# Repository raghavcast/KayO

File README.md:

# KayO
Head to releases and download the newest version.

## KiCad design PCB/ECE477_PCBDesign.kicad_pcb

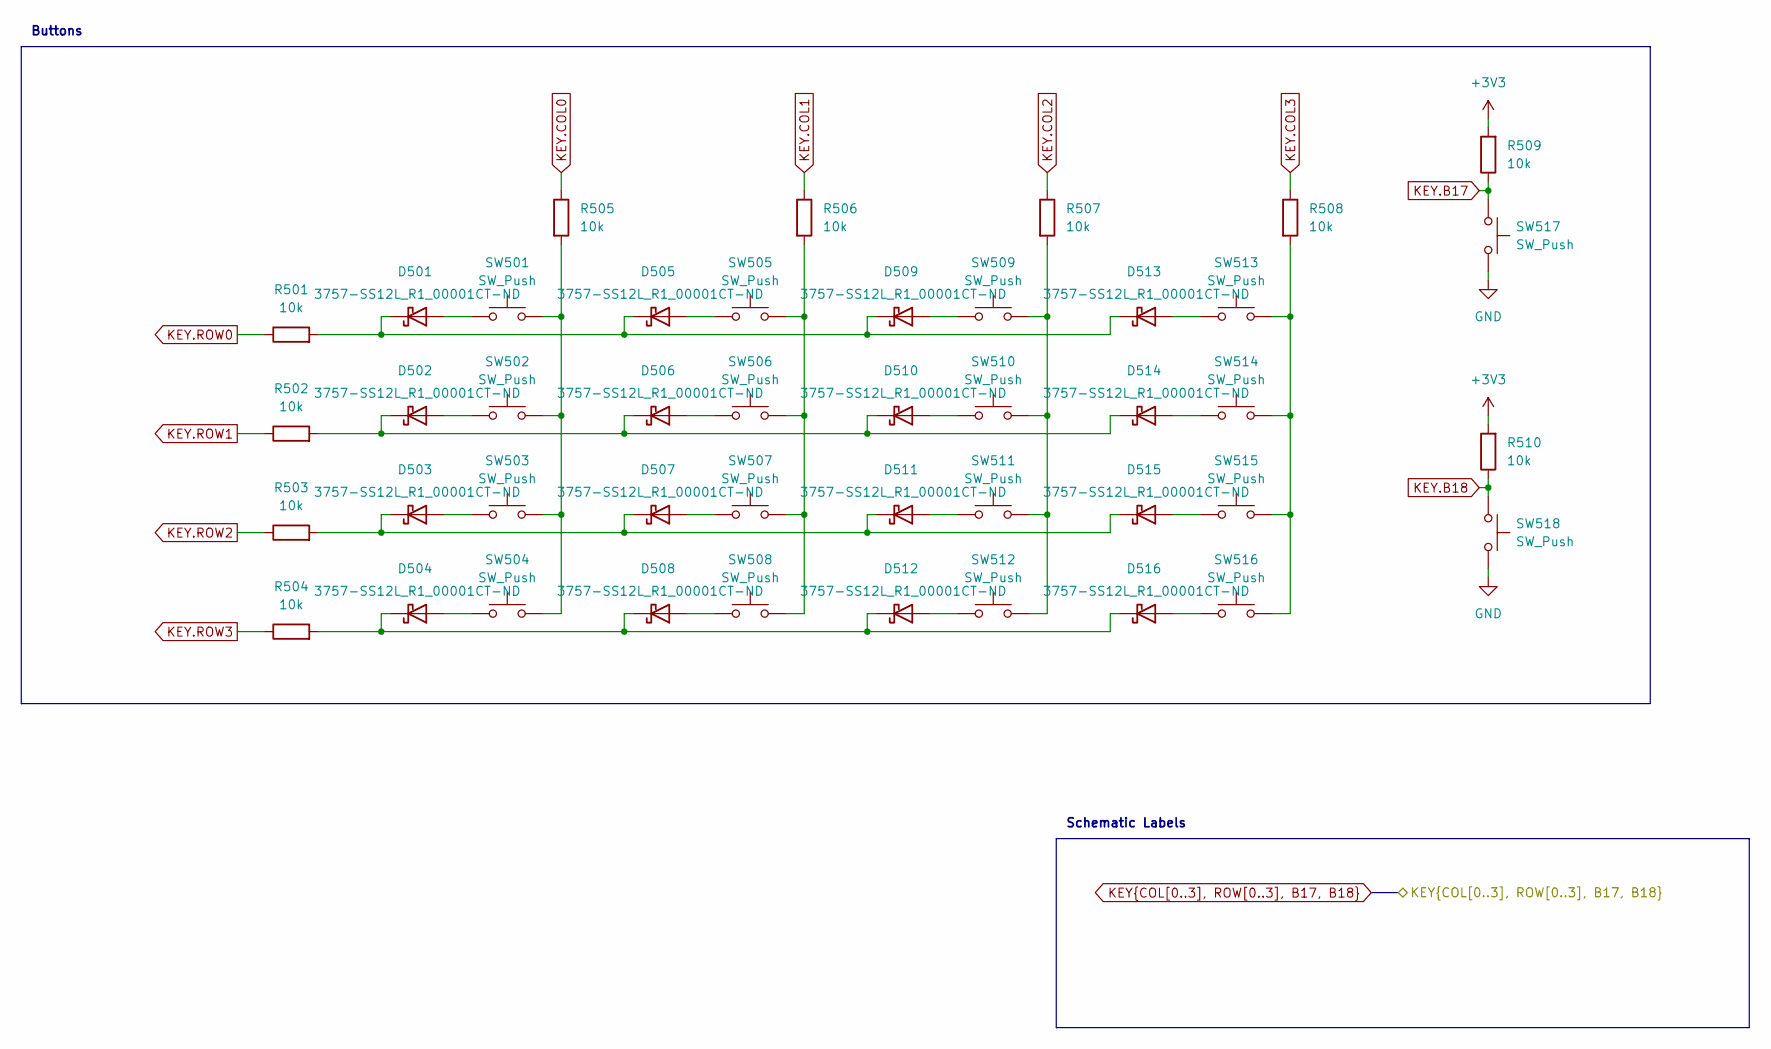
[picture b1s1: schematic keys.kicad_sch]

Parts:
D501, D502, D503, D504, D505, D506, D507, D508, D509, D510, D511, D512, D513, D514, D515, D516: 3757-SS12L_R1_00001CT-ND; D_SMA; Mfg. Part # SS12L_R1_00001; LCSC C36975
R501, R502, R503, R504, R505, R506, R507, R508, R509, R510: 10k; R_0603_1608Metric_Pad0.98x0.95mm_HandSolder; Mfg. Part # RC0603JR-0710KL; DigiKey Part 311-10KGRCT-ND
SW501, SW502, SW503, SW504, SW505, SW506, SW507, SW508, SW509, SW510, SW511, SW512, SW513, SW514, SW515, SW516, SW517, SW518: SW_Push; JST_XH_B2B-XH-A_1x02_P2.50mm_Vertical; Mfg. Part # B2B-XH-A; DigiKey Part 455-B2B-XH-A-ND

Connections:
+3V3: R509.2, R510.2; also elsewhere on the board
GND: SW517.2, SW518.2; also elsewhere on the board
KEY.B17: R509.1, SW517.1; also elsewhere on the board
KEY.B18: R510.1, SW518.1; also elsewhere on the board
KEY.COL0: R505.1; also elsewhere on the board
KEY.COL1: R506.1; also elsewhere on the board
KEY.COL2: R507.1; also elsewhere on the board
KEY.COL3: R508.1; also elsewhere on the board
KEY.ROW0: R501.1; also elsewhere on the board
KEY.ROW1: R502.1; also elsewhere on the board
KEY.ROW2: R503.1; also elsewhere on the board
KEY.ROW3: R504.1; also elsewhere on the board
unnamed: D501.2 (A), SW501.1
unnamed: D501.1 (K), D505.1 (K), D509.1 (K), D513.1 (K), R501.2
unnamed: D502.2 (A), SW502.1
unnamed: D502.1 (K), D506.1 (K), D510.1 (K), D514.1 (K), R502.2
unnamed: D503.2 (A), SW503.1
unnamed: D503.1 (K), D507.1 (K), D511.1 (K), D515.1 (K), R503.2
unnamed: D504.2 (A), SW504.1
unnamed: D504.1 (K), D508.1 (K), D512.1 (K), D516.1 (K), R504.2
unnamed: D505.2 (A), SW505.1
unnamed: D506.2 (A), SW506.1
unnamed: D507.2 (A), SW507.1
unnamed: D508.2 (A), SW508.1
unnamed: D509.2 (A), SW509.1
unnamed: D510.2 (A), SW510.1
unnamed: D511.2 (A), SW511.1
unnamed: D512.2 (A), SW512.1
unnamed: D513.2 (A), SW513.1
unnamed: D514.2 (A), SW514.1
unnamed: D515.2 (A), SW515.1
unnamed: D516.2 (A), SW516.1
unnamed: R505.2, SW501.2, SW502.2, SW503.2, SW504.2
unnamed: R506.2, SW505.2, SW506.2, SW507.2, SW508.2
unnamed: R507.2, SW509.2, SW510.2, SW511.2, SW512.2
unnamed: R508.2, SW513.2, SW514.2, SW515.2, SW516.2

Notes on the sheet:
Buttons
Schematic Labels

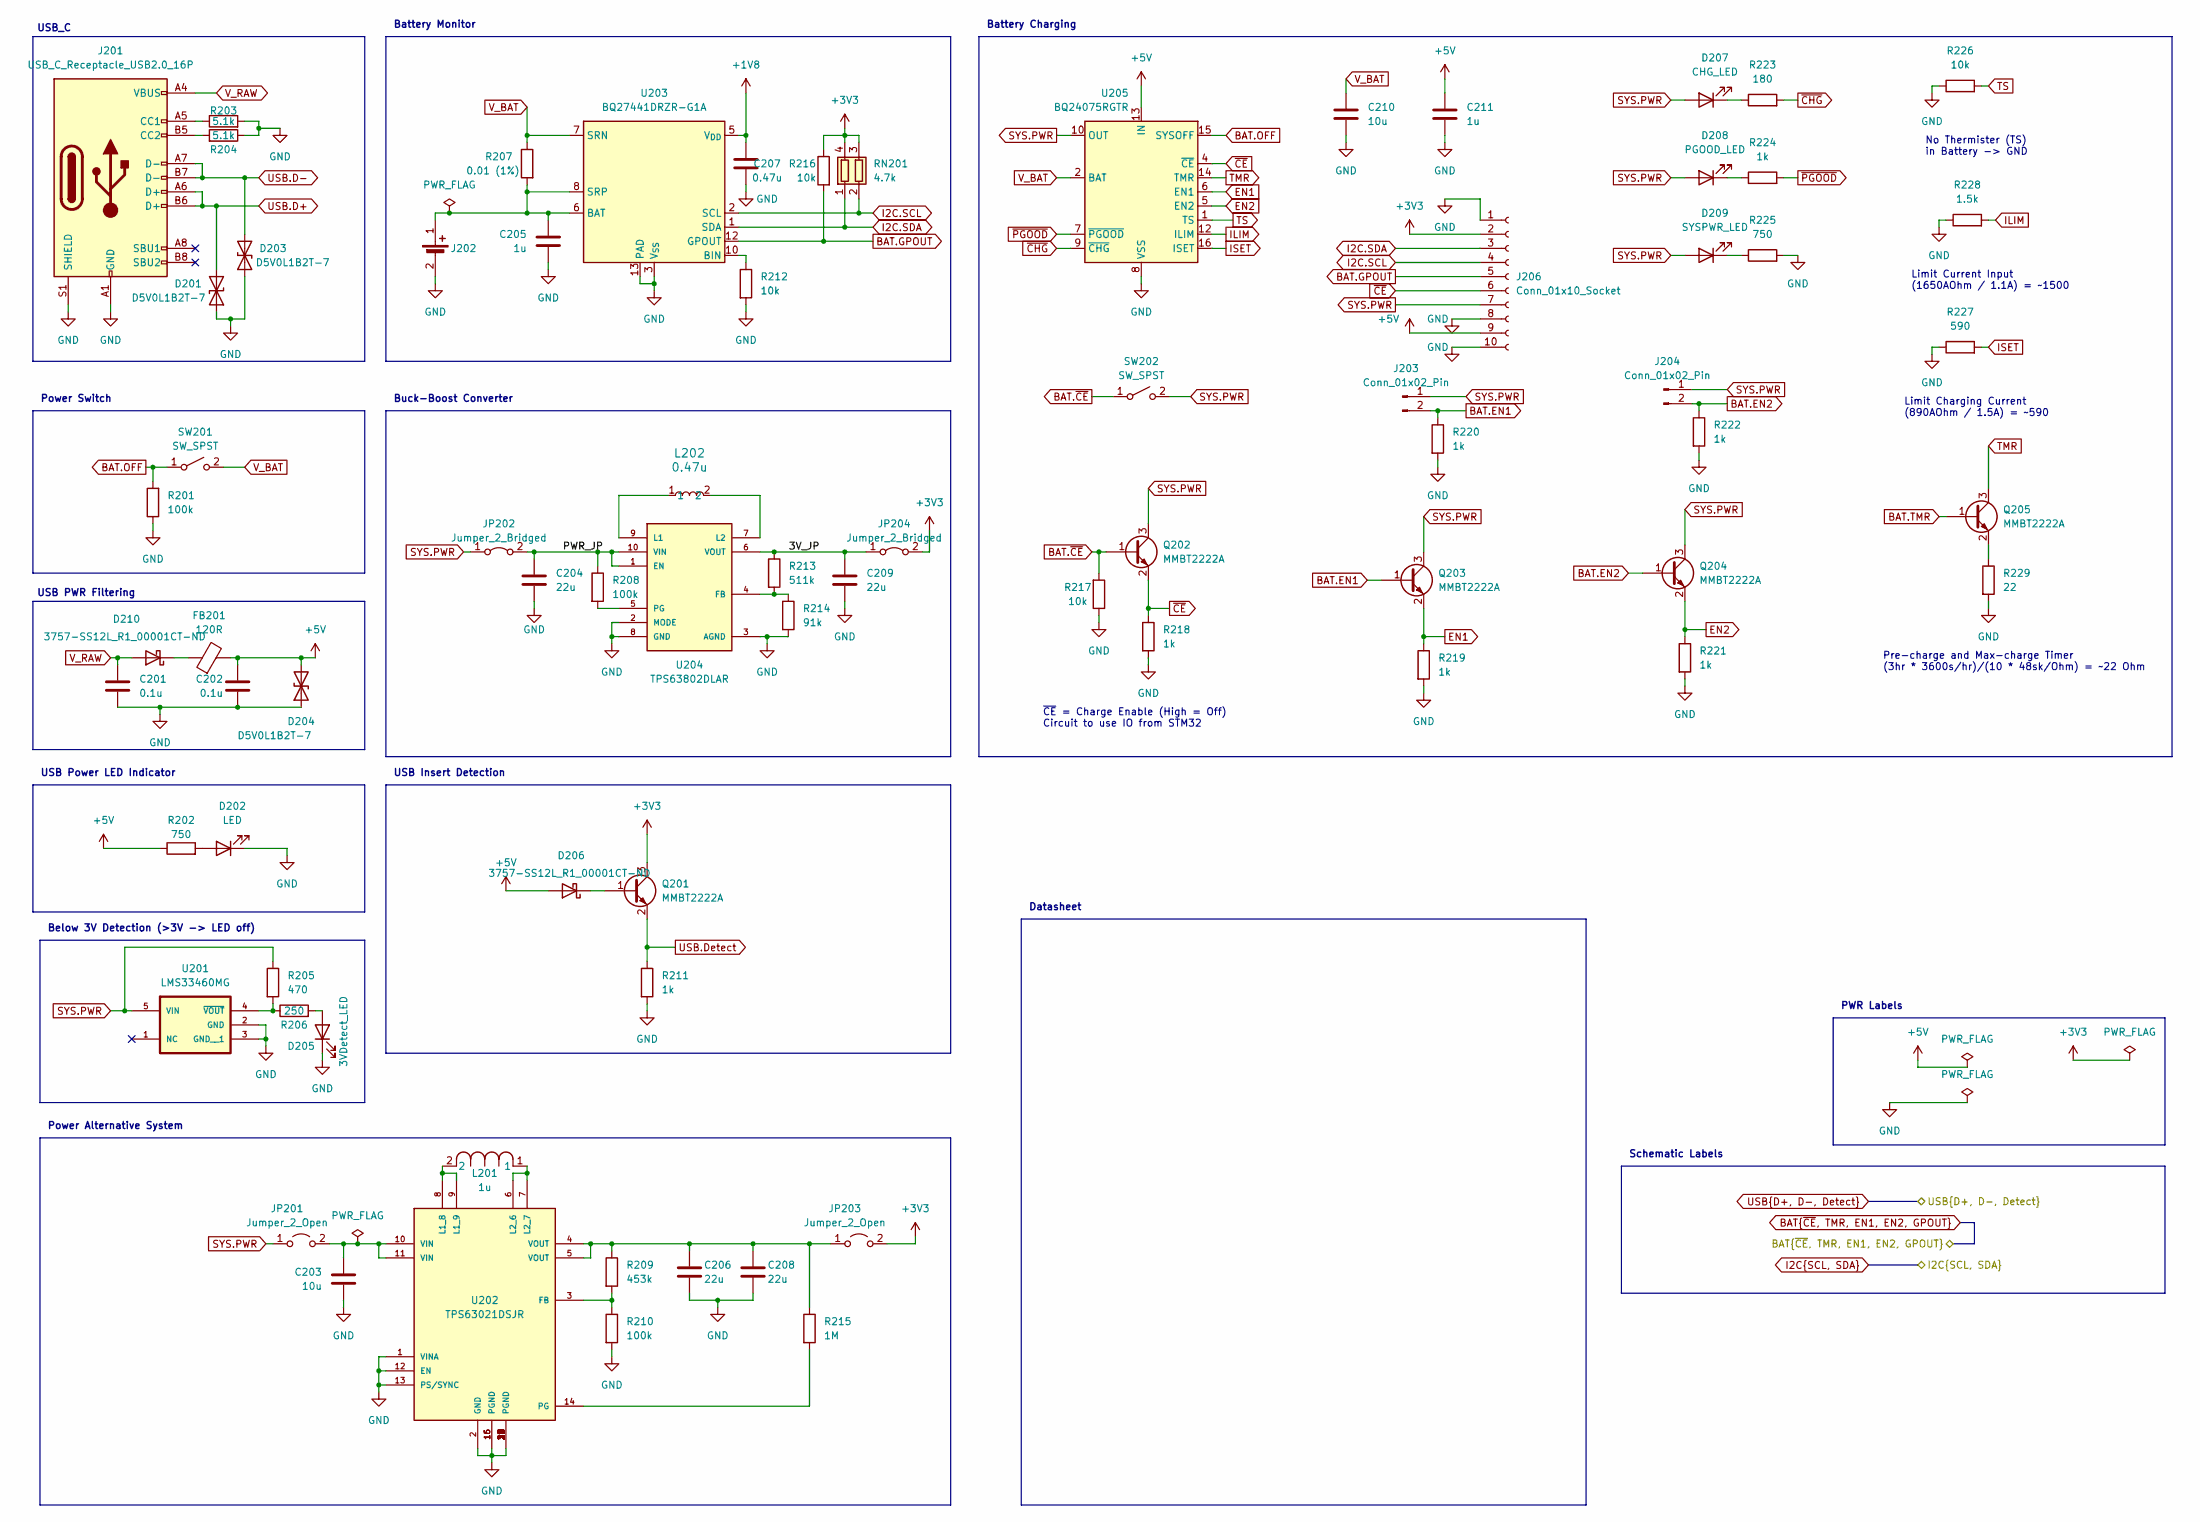
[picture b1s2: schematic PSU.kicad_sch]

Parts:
C201, C202: 0.1u; C_0603_1608Metric_Pad1.08x0.95mm_HandSolder; Mfg. Part # GRM033R61A104ME15D; LCSC C1525
C203: 10u; C_0603_1608Metric_Pad1.08x0.95mm_HandSolder; Mfg. Part # C1608X5R1E106M080AC; DigiKey Part 445-9015-1-ND
C204: 22u; C_0603_1608Metric_Pad1.08x0.95mm_HandSolder; Mfg. Part # GRM188R60J226MEA0D; DigiKey Part 490-7611-1-ND
C205, C211: 1u; C_0603_1608Metric_Pad1.08x0.95mm_HandSolder; Mfg. Part # GRM033R60J105MEA2D; DigiKey Part 490-7229-1-ND
C206, C208, C209: 22u; C_0603_1608Metric_Pad1.08x0.95mm_HandSolder; Mfg. Part # C1608X5R1A226M080AC; DigiKey Part 445-9077-1-ND
C207: 0.47u; C_0603_1608Metric_Pad1.08x0.95mm_HandSolder; Mfg. Part # C1608X7R1C474K080AC; DigiKey Part 445-5192-1-ND
C210: 10u; C_0603_1608Metric_Pad1.08x0.95mm_HandSolder; Mfg. Part # GRM188R60J106KE47J; DigiKey Part 490-GRM188R60J106KE47JCT-ND
D201, D203, D204: D5V0L1B2T-7; D_SOD-523; Mfg. Part # D5V0L1B2T-7; LCSC C508181
D202: LED; D_0805_2012Metric_Pad1.15x1.40mm_HandSolder; Mfg. Part # LS R976-NR-1; LCSC C136765
D205: 3VDetect_LED; D_0805_2012Metric_Pad1.15x1.40mm_HandSolder; Mfg. Part # LS R976-NR-1; LCSC C136765
D206, D210: 3757-SS12L_R1_00001CT-ND; D_SMA; Mfg. Part # SS12L_R1_00001; LCSC C36975
D207: CHG_LED; LED_0805_2012Metric_Pad1.15x1.40mm_HandSolder; Mfg. Part # LS R976-NR-1; DigiKey Part 475-LSR976-NR-1CT-ND
D208: PGOOD_LED; LED_0805_2012Metric_Pad1.15x1.40mm_HandSolder; Mfg. Part # LS R976-NR-1; DigiKey Part 475-LSR976-NR-1CT-ND
D209: SYSPWR_LED; LED_0805_2012Metric_Pad1.15x1.40mm_HandSolder; Mfg. Part # LS R976-NR-1; DigiKey Part 475-LSR976-NR-1CT-ND
FB201: 120R; L_0603_1608Metric; Mfg. Part # BLM18BD121SH1D; LCSC C279682
J201: USB_C_Receptacle_USB2.0_16P; USB_C_Receptacle_HRO_TYPE-C-31-M-12; Mfg. Part # USB4105-GF-A; DigiKey Part 2073-USB4105-GF-ACT-ND
J202: Conn_01x02_Pin; CONN_S2B-PH-K-S_JST; Mfg. Part # S2B-PH-K-S; DigiKey Part 455-1719-ND
J203, J204: Conn_01x02_Pin; PinHeader_1x02_P2.54mm_Vertical
J206: Conn_01x10_Socket; ECE477_BATBabySitter; Mfg. Part # N/A
JP201, JP203: Jumper_2_Open; SolderJumper-2_P1.3mm_Open_Pad1.0x1.5mm
JP202, JP204: Jumper_2_Bridged; SolderJumper-2_P1.3mm_Bridged_Pad1.0x1.5mm
L201: 1u; IND_XFL4020-102MEC; Mfg. Part # XFL4020-102MEC; DigiKey Part 2457-XFL4020-102MEC-ND
L202: 0.47u; IND_IHLP-2020CZ; Mfg. Part # IHLP2020CZERR47M11; DigiKey Part 541-1231-1-ND
Q201, Q202, Q203, Q204, Q205: MMBT2222A; SOT-23-3; Mfg. Part # MMBT2222A; DigiKey Part 4878-MMBT2222ACT-ND
R201, R208, R210: 100k; R_0603_1608Metric_Pad0.98x0.95mm_HandSolder; Mfg. Part # RC0603FR-07100KL; DigiKey Part 311-100KHRCT-ND
R202: 750; R_0603_1608Metric_Pad0.98x0.95mm_HandSolder; Mfg. Part # RC0603JR-07750RL; LCSC C103153
R203, R204: 5.1k; R_0603_1608Metric_Pad0.98x0.95mm_HandSolder; Mfg. Part # RMCF0603FT5K10; LCSC C105872
R205: 470; R_0603_1608Metric_Pad0.98x0.95mm_HandSolder; Mfg. Part # RC0603FR-13470RL; DigiKey Part 13-RC0603FR-13470RLCT-ND
R206: 250; R_0603_1608Metric_Pad0.98x0.95mm_HandSolder; Mfg. Part # RNCF0603TKY250R; DigiKey Part RNCF0603TKY250RCT-ND
R207: 0.01 (1%); R_0603_1608Metric_Pad0.98x0.95mm_HandSolder; Mfg. Part # WSL0603R0100FEA; DigiKey Part WSLJ-.01CT-ND
R209: 453k; R_0603_1608Metric_Pad0.98x0.95mm_HandSolder; Mfg. Part # RC0603FR-07453KL; DigiKey Part 311-453KHRCT-ND
R211, R218, R219, R220, R221, R222, R224: 1k; R_0603_1608Metric_Pad0.98x0.95mm_HandSolder; Mfg. Part # RC0603FR-071KL; DigiKey Part 311-1.00KHRCT-ND
R212, R216, R217, R226: 10k; R_0603_1608Metric_Pad0.98x0.95mm_HandSolder; Mfg. Part # RC0603JR-0710KL; DigiKey Part 311-10KGRCT-ND
R213: 511k; R_0603_1608Metric_Pad0.98x0.95mm_HandSolder; Mfg. Part # CRCW0603511KFKEA; DigiKey Part 541-511KHCT-ND
R214: 91k; R_0603_1608Metric_Pad0.98x0.95mm_HandSolder; Mfg. Part # RC0603FR-0791KL; DigiKey Part 311-91.0KHRCT-ND
R215: 1M; R_0603_1608Metric_Pad0.98x0.95mm_HandSolder; Mfg. Part # RC0603FR-071ML; DigiKey Part 311-1.00MHRCT-ND
R223: 180; R_0603_1608Metric_Pad0.98x0.95mm_HandSolder; Mfg. Part # RC0603FR-13180RL; DigiKey Part 13-RC0603FR-13180RLCT-ND
R225: 750; R_0603_1608Metric_Pad0.98x0.95mm_HandSolder; Mfg. Part # RC0603JR-07750RL; DigiKey Part 311-750GRCT-ND
R227: 590; R_0603_1608Metric_Pad0.98x0.95mm_HandSolder; Mfg. Part # RC0402FR-07590RL; DigiKey Part YAG3193CT-ND
R228: 1.5k; R_0603_1608Metric_Pad0.98x0.95mm_HandSolder; Mfg. Part # RC0603FR-131K5L; DigiKey Part 13-RC0603FR-131K5LCT-ND
R229: 22; R_0603_1608Metric_Pad0.98x0.95mm_HandSolder; Mfg. Part # RC0603FR-1322RL; DigiKey Part 13-RC0603FR-1322RLCT-ND
RN201: 4.7k; R_Array_Convex_2x0606; Mfg. Part # EXB-34V472JV; DigiKey Part Y8472CT-ND
SW201, SW202: SW_SPST; JST_XH_B2B-XH-A_1x02_P2.50mm_Vertical; Mfg. Part # B2B-XH-A; DigiKey Part 455-B2B-XH-A-ND
U201: LMS33460MG; SOT65P210X110-5N; Mfg. Part # LMS33460MG; DigiKey Part 296-LMS33460MGCT-ND
U202: TPS63021DSJR; IC_TPS63021DSJR
U203: BQ27441DRZR-G1A; Texas_S-PDSO-N12; Mfg. Part # BQ27441DRZR-G1A; DigiKey Part 296-39941-1-ND
U204: TPS63802DLAR; VREG_TPS63802DLAR; Mfg. Part # TPS63802DLAR; DigiKey Part 296-TPS63802DLARCT-ND
U205: BQ24075RGTR; VQFN-16-1EP_3x3mm_P0.5mm_EP1.6x1.6mm_ThermalVias; Mfg. Part # BQ24075RGTR; DigiKey Part 296-38874-1-ND

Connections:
+1V8: C207.1, U203.5 (V_{DD})
+3V3: J206.2, JP203.2 (B), JP204.2 (B), Q201.3 (C), R216.1, RN201.3 (R2.2), RN201.4 (R1.2); also elsewhere on the board
+5V: C202.1, C211.1, D204.2 (A2), D206.2 (A), FB201.2, J206.9, R202.1, U205.13 (IN); also elsewhere on the board
/Power Supply Unit/3V_JP: C209.1, JP204.1 (A), R213.1, U204.6 (VOUT)
/Power Supply Unit/PWR_JP: C204.1, JP202.2 (B), R208.1, U204.1 (EN), U204.10 (VIN)
BAT.EN1: J203.2, Q203.1 (B), R220.1; also elsewhere on the board
BAT.EN2: J204.2, Q204.1 (B), R222.1; also elsewhere on the board
BAT.GPOUT: J206.5, R216.2, U203.12 (GPOUT); also elsewhere on the board
BAT.OFF: R201.2, SW201.1 (A), U205.15 (SYSOFF)
BAT.TMR: Q205.1 (B); also elsewhere on the board
BAT.~CE: Q202.1 (B), R217.2, SW202.1 (A); also elsewhere on the board
EN1: Q203.2 (E), R219.1, U205.6 (EN1)
EN2: Q204.2 (E), R221.1, U205.5 (EN2)
GND: C201.2, C202.2, C203.2, C204.2, C205.1, C206.2, C207.2, C208.2, C209.2, C210.2, C211.2, D201.1 (A1), D202.1 (K), D203.1 (A1), D204.1 (A1), D205.1 (K), J201.A1 (GND), J201.A12 (GND), J201.B1 (GND), J201.B12 (GND), J201.S1 (SHIELD), J202.2, J206.1, J206.8, J206.10, R201.1, R203.2, R204.1, R210.2, R211.2, R212.2, R214.2, R217.1, R218.2, R219.2, R220.2, R221.2, R222.2, R225.2, R226.1, R227.1, R228.1, R229.2, U201.2 (GND), U201.3 (GND__1), U202.1 (VINA), U202.2 (GND), U202.12 (EN), U202.13 (PS/SYNC), U202.15 (PGND), U202.16 (PGND), U202.17 (PGND), U202.18 (PGND), U202.19 (PGND), U202.20 (PGND), U202.21 (PGND), U202.22 (PGND), U202.23 (PGND), U202.24 (PGND), U202.25 (PGND), U202.26 (PGND), U202.27 (PGND), U202.28 (PGND), U202.29 (PGND), U202.30 (PGND), U203.3 (V_{SS}), U203.13 (PAD), U204.2 (MODE), U204.3 (AGND), U204.8 (GND), U205.8 (VSS), U205.17 (VSS); also elsewhere on the board
I2C.SCL: J206.4, RN201.2 (R2.1), U203.2 (SCL); also elsewhere on the board
I2C.SDA: J206.3, RN201.1 (R1.1), U203.1 (SDA); also elsewhere on the board
ILIM: R228.2, U205.12 (ILIM)
ISET: R227.2, U205.16 (ISET)
unnamed: D202.2 (A), R202.2
unnamed: D205.2 (A), R206.2
unnamed: D206.1 (K), Q201.1 (B)
unnamed: D207.1 (K), R223.1
unnamed: D208.1 (K), R224.1
unnamed: D209.1 (K), R225.1
unnamed: D210.1 (K), FB201.1
unnamed: J201.A5 (CC1), R203.1
unnamed: J201.B5 (CC2), R204.2
unnamed: C205.2, J202.1, R207.2, U203.6 (BAT), U203.8 (SRP)
unnamed: C203.1, JP201.2 (B), U202.10 (VIN), U202.11 (VIN)
unnamed: C206.1, C208.1, JP203.1 (A), R209.1, R215.1, U202.4 (VOUT), U202.5 (VOUT)
unnamed: Q205.2 (E), R229.1
unnamed: R205.2, R206.1, U201.4 (~VOUT)
unnamed: R209.2, R210.1, U202.3 (FB)
unnamed: L201.2, U202.8 (L1_8), U202.9 (L1_9)
unnamed: L201.1, U202.6 (L2_6), U202.7 (L2_7)
unnamed: R215.2, U202.14 (PG)
unnamed: R212.1, U203.10 (BIN)
unnamed: R213.2, R214.1, U204.4 (FB)
unnamed: L202.1, U204.9 (L1)
unnamed: L202.2, U204.7 (L2)
unnamed: R208.2, U204.5 (PG)
SYS.PWR: D207.2 (A), D208.2 (A), D209.2 (A), J203.1, J204.1, J206.7, JP201.1 (A), JP202.1 (A), Q202.3 (C), Q203.3 (C), Q204.3 (C), R205.1, SW202.2 (B), U201.5 (VIN), U205.10 (OUT), U205.11 (OUT)
TMR: Q205.3 (C), U205.14 (TMR)
TS: R226.2, U205.1 (TS)
USB.D+: D201.2 (A2), J201.A6 (D+), J201.B6 (D+); also elsewhere on the board
USB.D-: D203.2 (A2), J201.A7 (D-), J201.B7 (D-); also elsewhere on the board
USB.Detect: Q201.2 (E), R211.1; also elsewhere on the board
V_BAT: C210.1, R207.1, SW201.2 (B), U203.7 (SRN), U205.2 (BAT), U205.3 (BAT)
V_RAW: C201.1, D210.2 (A), J201.A4 (VBUS), J201.A9 (VBUS), J201.B4 (VBUS), J201.B9 (VBUS)
~CE: J206.6, Q202.2 (E), R218.1, U205.4 (~CE)
~CHG: R223.2, U205.9 (~CHG)
~PGOOD: R224.2, U205.7 (~PGOOD)

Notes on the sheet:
USB PWR Filtering
Battery Monitor
Datasheet
USB_C
Limit Current Input (1650AOhm / 1.1A) = ~1500
No Thermister (TS) in Battery -> GND
Below 3V Detection (>3V -> LED off)
USB Insert Detection
Limit Charging Current (890AOhm / 1.5A) = ~590
Pre-charge and Max-charge Timer (3hr * 3600s/hr)/(10 * 48sk/Ohm) = ~22 Ohm
Schematic Labels
Power Alternative System
Buck-Boost Converter
~{CE} = Charge Enable (High = Off) Circuit to use IO from STM32
PWR Labels
Power Switch
USB Power LED Indicator
Battery Charging

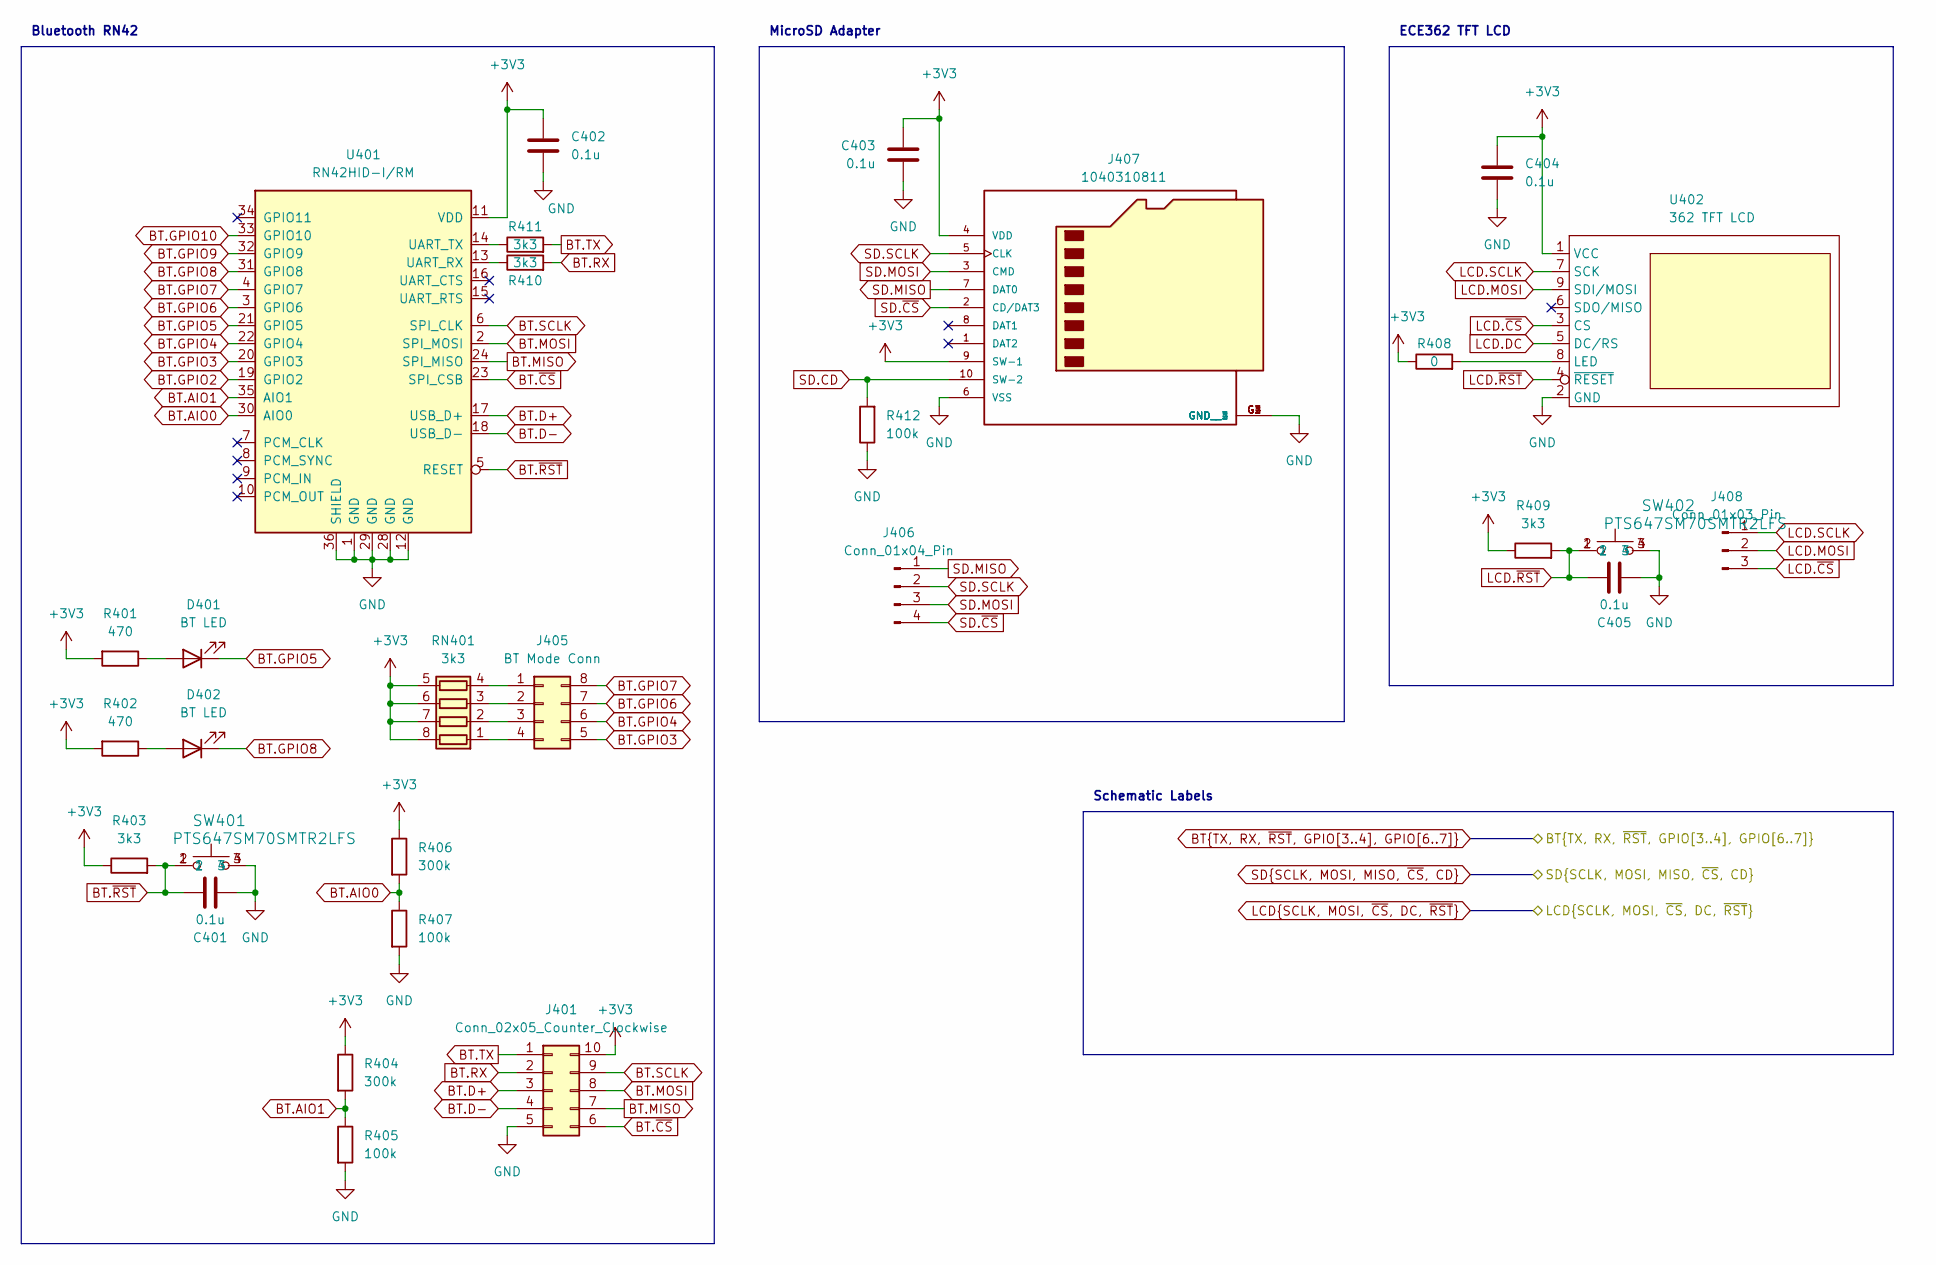
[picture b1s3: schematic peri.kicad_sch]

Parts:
C401, C402, C403, C404, C405: 0.1u; C_0603_1608Metric_Pad1.08x0.95mm_HandSolder; Mfg. Part # GRM033R61A104ME15D; DigiKey Part 490-5405-1-ND
D401, D402: BT LED; LED_0805_2012Metric_Pad1.15x1.40mm_HandSolder; Mfg. Part # LS R976-NR-1; DigiKey Part 475-LSR976-NR-1CT-ND
J401: Conn_02x05_Counter_Clockwise; PinHeader_2x05_P2.54mm_Vertical
J405: BT Mode Conn; PinHeader_2x04_P2.54mm_Vertical
J406: Conn_01x04_Pin; PinHeader_1x04_P2.54mm_Vertical
J407: 1040310811; MOLEX_104031-0811; Mfg. Part # 1040310811; DigiKey Part WM6357CT-ND
J408: Conn_01x03_Pin; PinHeader_1x03_P2.54mm_Vertical
R401, R402: 470; R_0603_1608Metric_Pad0.98x0.95mm_HandSolder; Mfg. Part # RC0603FR-13470RL; DigiKey Part 13-RC0603FR-13470RLCT-ND
R403, R409, R410, R411: 3k3; R_0603_1608Metric_Pad0.98x0.95mm_HandSolder; Mfg. Part # RC0603FR-133K3L; DigiKey Part 13-RC0603FR-133K3LCT-ND
R404, R406: 300k; R_0603_1608Metric_Pad0.98x0.95mm_HandSolder; Mfg. Part # RC0603FR-07300KL; DigiKey Part YAG2585CT-ND
R405, R407, R412: 100k; R_0603_1608Metric_Pad0.98x0.95mm_HandSolder; Mfg. Part # RC0603FR-07100KL; DigiKey Part 311-100KHRCT-ND
R408: 0; R_0603_1608Metric_Pad0.98x0.95mm_HandSolder; Mfg. Part # RC0603JR-070RL; DigiKey Part 311-0.0GRCT-ND
RN401: 3k3; R_Array_Convex_4x1206; Mfg. Part # YC164-FR-073K32L; DigiKey Part 13-YC164-FR-073K32LCT-ND
SW401, SW402: PTS647SM70SMTR2LFS; PTS647SM70SMTR2LFS_CNK; Mfg. Part # PTS 647 SM70 SMTR2 LFS; DigiKey Part PTS647SM70SMTR2LFSCT-ND
U401: RN42HID-I/RM; RN42; Mfg. Part # RN42HID-I/RM; DigiKey Part RN42HID-I/RM-ND
U402: 362 TFT LCD; PinHeader_1x09_P2.54mm_Vertical

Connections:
+3V3: C402.1, C403.1, C404.1, J401.10, J407.4 (VDD), J407.9 (SW-1), R401.2, R402.2, R403.1, R404.1, R406.1, R408.1, R409.1, RN401.5 (R4.2), RN401.6 (R3.2), RN401.7 (R2.2), RN401.8 (R1.2), U401.11 (VDD), U402.1 (VCC); also elsewhere on the board
BT.AIO0: R406.2, R407.1, U401.30 (AIO0)
BT.AIO1: R404.2, R405.1, U401.35 (AIO1)
BT.D+: J401.3, U401.17 (USB_D+)
BT.D-: J401.4, U401.18 (USB_D-)
BT.GPIO2: U401.19 (GPIO2)
BT.GPIO3: J405.5, U401.20 (GPIO3); also elsewhere on the board
BT.GPIO4: J405.6, U401.22 (GPIO4); also elsewhere on the board
BT.GPIO5: D401.1 (K), U401.21 (GPIO5)
BT.GPIO6: J405.7, U401.3 (GPIO6); also elsewhere on the board
BT.GPIO7: J405.8, U401.4 (GPIO7); also elsewhere on the board
BT.GPIO8: D402.1 (K), U401.31 (GPIO8)
BT.GPIO9: U401.32 (GPIO9)
BT.GPIO10: U401.33 (GPIO10)
BT.MISO: J401.7, U401.24 (SPI_MISO)
BT.MOSI: J401.8, U401.2 (SPI_MOSI)
BT.RX: J401.2, R410.2; also elsewhere on the board
BT.SCLK: J401.9, U401.6 (SPI_CLK)
BT.TX: J401.1, R411.2; also elsewhere on the board
BT.~CS: J401.6, U401.23 (SPI_CSB)
BT.~RST: C401.2, R403.2, SW401.1, SW401.2, U401.5 (RESET)
GND: C401.1, C402.2, C403.2, C404.2, C405.1, J401.5, J407.6 (VSS), J407.G1 (GND__1), J407.G2 (GND__2), J407.G3 (GND__3), J407.G4 (GND__4), R405.2, R407.2, R412.1, SW401.3, SW401.4, SW402.3, SW402.4, U401.1 (GND), U401.12 (GND), U401.28 (GND), U401.29 (GND), U401.36 (SHIELD), U402.2 (GND); also elsewhere on the board
LCD.DC: U402.5 (DC/RS); also elsewhere on the board
LCD.MOSI: J408.2, U402.9 (SDI/MOSI); also elsewhere on the board
LCD.SCLK: J408.1, U402.7 (SCK); also elsewhere on the board
LCD.~CS: J408.3, U402.3 (CS); also elsewhere on the board
LCD.~RST: C405.2, R409.2, SW402.1, SW402.2, U402.4 (~RESET); also elsewhere on the board
unnamed: D401.2 (A), R401.1
unnamed: D402.2 (A), R402.1
unnamed: J405.1, RN401.4 (R4.1)
unnamed: J405.2, RN401.3 (R3.1)
unnamed: J405.3, RN401.2 (R2.1)
unnamed: J405.4, RN401.1 (R1.1)
unnamed: R410.1, U401.13 (UART_RX)
unnamed: R411.1, U401.14 (UART_TX)
unnamed: R408.2, U402.8 (LED)
SD.CD: J407.10 (SW-2), R412.2; also elsewhere on the board
SD.MISO: J406.1, J407.7 (DAT0); also elsewhere on the board
SD.MOSI: J406.3, J407.3 (CMD); also elsewhere on the board
SD.SCLK: J406.2, J407.5 (CLK); also elsewhere on the board
SD.~CS: J406.4, J407.2 (CD/DAT3); also elsewhere on the board

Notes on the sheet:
Bluetooth RN42
Schematic Labels
ECE362 TFT LCD
MicroSD Adapter
